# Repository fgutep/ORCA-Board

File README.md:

<div align="center">

<br>

**Tarjeta de control abierta para robots con ROS 2, pensada para ser la base electrónica compartida de los robots de la universidad.**

<br>

[Resumen](#resumen) · [Características](#características) · [Estado](#estado-del-proyecto) · [Integración en robots](#integración-en-robots) · [Inicio rápido](#inicio-rápido) · [Estructura](#estructura-del-repositorio) · [Simulación](#simulación-de-la-etapa-de-potencia) · [Equipo](#equipo) · [Licencia](#licencia)

</div>

---

## Resumen

En la robótica académica cada proyecto suele diseñar desde cero su electrónica de potencia, actuación y sensado, y después improvisa puentes para conectarla con ROS 2. Eso repite el mismo trabajo de hardware y firmware en cada equipo. Las tarjetas comerciales de referencia, como la Acebott V3 o la Hiwonder RCB, aceptan como máximo baterías 2S o 3S, no siempre traen bus CAN y necesitan un computador intermedio para hablar con ROS.

**ORCA-Board** (*Open Robotics Control Architecture*) es una tarjeta de control abierta pensada para funcionar como nodo nativo de ROS 2 con micro-ROS. Se alimenta con baterías LiPo de **2S a 6S (7.4 a 25.2 V)** y reúne en una sola placa lo que un robot móvil o un brazo necesitan para actuar, sentir y comunicarse. El objetivo del proyecto es diseñar, fabricar y verificar esta plataforma para que distintos robots compartan la misma base electrónica.

<table>
  <tr>
    <td align="center" width="33%"><br><sub><b>Placa de control</b> · ESP32-S3</sub></td>
    <td align="center" width="33%"><br><sub><b>Placa de potencia</b> · LM5175</sub></td>
    <td align="center" width="33%"><br><sub><b>Layout PCB</b> · placa de control (KiCad)</sub></td>
  </tr>
</table>

## Características

El sistema se divide en **dos PCB de 4 capas** diseñadas en KiCad.

### Placa de control

| Función | Componente |
|---|---|
| Microcontrolador | ESP32-S3-WROOM-1-N4 (Wi-Fi, BLE y USB nativo; 4 MB de flash, sin PSRAM) |
| Motores DC | 2 × drivers DRV8874 |
| Servos | 16 canales PWM con PCA9685 |
| IMU | BNO085 de 9 ejes |
| Voltaje de batería | INA226 |
| Corriente de batería | ACS725 |
| Bus CAN | Transceptor SN65HVD230 |
| Sensores externos | Multiplexor I²C TCA9548A (4 canales: J14–J17) |
| Alimentación lógica | Buck TPS54331D a 5 V y regulador de 3.3 V |

### Placa de potencia

Convertidor **buck-boost LM5175** para el riel de motores: entrada de 6 a 25.2 V, salida ajustable de 6.8 a 25 V y hasta 8 A.

| Función | Componente |
|---|---|
| Controlador | U1: LM5175PWPR, controlador buck-boost de 4 interruptores |
| Interruptores de potencia | Q1–Q4: MOSFET de canal N de 40 V en LFPAK56 (Nexperia BUK9Y3R5-40E, marcado 93E540) |
| Inductor | L1: Pulse PA4344, 4.7 µH |
| Sensado de corriente | R12: shunt Kelvin de 5 mΩ (2512) |
| Condensadores de potencia | Entrada: C2, 100 µF · Salida: C19 y C20, 220 µF · Cerámicos de 10 µF: C4, C14 y C15 |
| Ajuste de VOUT | Divisor de realimentación (R13 49.9 kΩ, R14 1.65 kΩ) y trimmer RV1 |
| Diodos | D1–D3: Schottky B5819W (bootstrap) |
| Conectores | J1 y J2: XT60 (entrada de batería y salida al riel de motores) |

### Mapa de pines (control Rev A)

| Bus / señal | Pines |
|---|---|
| I²C de placa (INA226 `0x40`, PCA9685 `0x41`, BNO085 `0x4A`/`0x4B`) | SDA `IO18` · SCL `IO17` |
| I²C externo (TCA9548A `0x70`) | SDA `IO39` · SCL `IO38` · RESET `IO40` |
| Sensor de corriente ACS725 | `IO9` |
| CAN (500 kbit/s) | TX `IO6` · RX `IO7` |

## Estado del proyecto

| Parte | Estado |
|---|---|
| **Placa de control, Rev A** | ✅ Fabricada y operativa. Autoprueba: **8 pruebas aprobadas, 0 fallas** |
| BNO085 | ✅ Montado (U1) y usado por el firmware micro-ROS (`/imu`) |
| Placa de potencia (LM5175), Placa 2 | ✅ Caracterizada con carga hasta 198.7 W en boost ([registro](Hardware-Potencia/pruebas_carga/registro.md)). Corta solo en la zona de transición (Vin ≈ Vout). Alimentó los motores a 12 V con la entrada barrida de 8 a 24 V |
| Placa de potencia (LM5175), Placa 1 | 🔴 LM5175 defectuoso de fábrica ([registro](Hardware-Potencia/physical_debug/README.md)) |
| Drivers de motor (DRV8874) | ✅ Probados con N20 y Faulhaber a 12 V en el banco de motores ([ensayo](Hardware/physical_debug/11_ensayo_motores_N20_Faulhaber.md)) |
| micro-ROS sobre la placa | ✅ Firmware de uso general ([`firmware/orca_micro_ros`](firmware/orca_micro_ros/README.md)): nodo `/orca_board` en ROS 2 Jazzy con batería, IMU, diagnóstico, motores, servos, puente CAN a 25 kbit/s (`can_msgs/Frame`) y parámetros persistentes, con transportes USB y Wi-Fi. Probado por USB y por Wi-Fi en la integración con SWARM; falta probar CAN contra otro nodo |
| Integración en robots | ✅ Robot del enjambre SWARM y robot diferencial con ROS 2 ([ver sección](#integración-en-robots)) |

### Resultados de la placa de control

| Prueba | Resultado medido | Estado |
|---|---|:---:|
| USB-C nativo | Enumera como `303a:1001`; flasheo con hash verificado | ✅ |
| Alimentación | Riel de 3.3 V estable; VBUS de 8 a 22 V con Wi-Fi activo | ✅ |
| Bus I²C | Detecta `0x40` (INA226), `0x41` (PCA9685) y `0x70` (TCA9548A) | ✅ |
| INA226 · V batería | ID `0x5449` leído; Vbus medido = 8.001 V | ✅ |
| PCA9685 · 16 PWM | Escritura y lectura de registros correcta | ✅ |
| ACS725 · corriente | Cero calibrado en 319 mV, sensibilidad 264 mV/A | ✅ |
| CAN · SN65HVD230 | Eco a 500 kbit/s con 0 errores de bus | ✅ |
| Telemetría Wi-Fi | Autoprueba servida en `http://192.168.4.1` | ✅ |

<table>
  <tr>
    <td align="center" width="50%"><br><sub><b>Termografía con VBUS</b> · máx. 39.6 °C</sub></td>
    <td align="center" width="25%"><h1>8/8</h1><sub>pruebas aprobadas en la autoprueba (0 fallas)</sub></td>
    <td align="center" width="25%"><h1>8–22 V</h1><sub>VBUS estable con telemetría Wi-Fi activa</sub></td>
  </tr>
</table>

La termografía con VBUS dio un máximo de 39.6 °C. El detalle del bring-up, con errata y retrabajos incluidos, está en [`Hardware/physical_debug`](Hardware/physical_debug/README.md).

## Integración en robots

### Enjambre SWARM

La placa de control ORCA, integrada a un robot SWARM, respondió correctamente a señales de movimiento enviadas por Wi-Fi desde ROS 2 corriendo en una Raspberry Pi 5 que tenía esclavizada a la placa de lógica. Video de la validación: [youtu.be/ohQkxq8agtg](https://youtu.be/ohQkxq8agtg).

<table>
  <tr>
    <td align="center" width="50%"><br><sub>Robot SWARM antes de integrar ORCA</sub></td>
    <td align="center" width="50%"><br><sub>Robot SWARM con ORCA integrada</sub></td>
  </tr>
</table>

### Robot diferencial

ORCA en un robot diferencial con micro-ROS, ROS 2 y reconocimiento visual tipo TurtleBot. Video: [youtube.com/shorts/Cfd5DdbkZio](https://youtube.com/shorts/Cfd5DdbkZio).

<table>
  <tr>
    <td align="center" width="50%"></td>
    <td align="center" width="50%"></td>
  </tr>
</table>

## Inicio rápido

### 1. Flashear el firmware de autoprueba

El firmware vive en [`Hardware/physical_debug/`](Hardware/physical_debug/). La imagen más completa es [`orca_selftest`](Hardware/physical_debug/orca_selftest/orca_selftest.ino).

**Arduino IDE** (Herramientas →):

| Opción | Valor |
|---|---|
| Placa | ESP32S3 Dev Module |
| USB Mode | Hardware CDC and JTAG |
| USB CDC On Boot | **Enabled** |
| Flash Mode / Size | QIO 80MHz / 4MB (32Mb) |
| Partition Scheme | Default 4MB with spiffs |

**PlatformIO**: el proyecto de [`platformio_bringup/`](Hardware/physical_debug/platformio_bringup/platformio.ini) ya trae la configuración de la placa.

```bash
cd Hardware/physical_debug/platformio_bringup
pio run -t upload
pio device monitor        # 115200 baudios por el USB nativo
```

### 2. Ver la autoprueba

Cada 5 s la placa corre todas las pruebas y publica el informe por **USB** y por **Wi-Fi**.

1. Conéctate a la red `ORCA-Board` (la clave está en el sketch; cámbiala si vas a usar la placa fuera del laboratorio).
2. Abre **http://192.168.4.1/** para ver el informe en vivo.
3. Opcional: `/status.json` (telemetría y resultados) y `/report.txt` (informe en texto).

### 3. Registrar telemetría desde el PC

```bash
python3 Hardware/physical_debug/wifi_telemetry/orca_monitor.py --csv prueba.csv
```

Solo usa la biblioteca estándar de Python, guarda todo en CSV y avisa si la placa deja de responder o se reinicia.

## Estructura del repositorio

```text
ORCA-Board/
├── Hardware/                  PCB de control (KiCad): esquemáticos, PCB, footprints y gerbers
│   └── physical_debug/        Bring-up de la placa fabricada: documentos 01–09 y firmware de prueba
├── Hardware-Potencia/         PCB de potencia LM5175 (KiCad) y su bring-up
│   ├── jlcpcb/                Archivos de fabricación y BOM de potencia (production_files/)
│   ├── pruebas_carga/         Script, registro y datos de las pruebas de carga
│   └── physical_debug/        Protocolo de arranque por etapas y diagnóstico
├── simulacion/                Modelos y simulaciones LTspice del buck-boost
│   ├── scripts/               Análisis y gráficas en Python
│   └── resultados/            Figuras de las corridas
├── firmware/
│   └── orca_micro_ros/        Firmware micro-ROS (ROS 2 Jazzy) de uso general
├── examples/                  Ejemplos de uso de la placa (brazo por gestos con IMU y servos)
├── Datasheets/                Hojas de datos de los componentes
├── Prints/                    Esquemático y layout de la placa de potencia en PDF/PNG
└── docs/img/                  Imágenes de este README
```

## Simulación de la etapa de potencia

<p align="center">
  <br>
  <sub><b>Layout PCB</b> · placa de potencia, cara superior (KiCad)</sub>
</p>

La carpeta [`simulacion/`](simulacion/) contiene el modelo LTspice del LM5175 y el barrido de **4 esquinas** (corrida del 29-ago) con escalón de carga de 2 A a 8.4 A a los 24 ms, contrastado con los límites de diseño de 8 A continuos y 15 A de pico en el inductor.

| VIN | VOUT esperado | VOUT simulado | Desviación | I_L pico | Pin | Pout | Eficiencia |
|---|---|---|---|---|---|---|---|
| 6 V | 7.2 V | 7.199 V | −0.01 % | 13.0 A | 69.4 W | 60.5 W | 87.2 % |
| 12 V | 12 V | 11.999 V | −0.01 % | 11.2 A | 109.0 W | 100.8 W | 92.4 % |
| 22.2 V | 25 V | 24.997 V | −0.01 % | 14.3 A | 219.4 W | 210.0 W | 95.7 % |
| 25.2 V | 7.2 V | 7.199 V | −0.01 % | 10.8 A | 69.2 W | 60.5 W | 87.4 % |

Las cuatro esquinas regulan dentro de ±0.01 % y mantienen el pico del inductor bajo 15 A (el menor margen es 0.7 A, en 22.2 → 25 V). VOUT simulado, Pin, Pout y eficiencia se miden en la ventana de 27 a 28 ms, con el escalón de carga aplicado. Datos completos en [`simulacion/resultados/c2_4esquinas_resumen.csv`](simulacion/resultados/c2_4esquinas_resumen.csv).

> **Nota sobre el barrido de 16 esquinas (28-ago).** Fue una corrida preliminar y se descartó como referencia: los cuatro casos de VIN = 6 V no arrancan (VOUT final de −1.55 V) y en los demás el pico del inductor llega a 34–37 A, por encima del límite de 15 A. Ese export tampoco registra la corriente de entrada, así que no permite calcular Pin ni eficiencia. Sus resultados siguen en [`simulacion/resultados/c1_16esquinas_resumen.csv`](simulacion/resultados/c1_16esquinas_resumen.csv) y su gráfica en [`c1_16esquinas_resumen.png`](simulacion/resultados/c1_16esquinas_resumen.png) solo como registro. La referencia vigente es la de 4 esquinas.

### Simulación frente a pruebas físicas

Las pruebas de carga se hicieron sobre la Placa 2 el 23 y 24 de noviembre, con la carga electrónica Rigol DL3021, la fuente EA PS 10060-170 y la cámara térmica Keysight U5855A. El detalle de cada corrida está en el [registro](Hardware-Potencia/pruebas_carga/registro.md).

**Pruebas realizadas**

| Corrida | VIN → VOUT | Tipo de prueba | Carga aplicada | Eficiencia medida |
|---|---|---|---|---|
| R08 | 12 → 12 V | Escalones de 0.5 A cada 30 s | 0.5 a 4.5 A (6 a 54 W) | 71.5 a 92.3 % |
| R09 | 16 → 12 V | Escalones de 0.25 A cada 20 s | 3 a 5 A (36 a 59.5 W) | 89.6 a 90.7 % |
| R10 | 9 → 12 V | Escalones de 0.25 A cada 20 s | 3 a 5 A (36 a 59.5 W) | 87.0 a 90.4 % |
| R11 | 20 → 12 V | Escalones de 0.25 A cada 20 s | 3 a 5 A (36 a 59.5 W) | 88 a 92 % |
| R12 a R15 | 10.5, 11, 13 y 14 → 12 V | Mapeo de la zona de transición | 4 a 5 A (48 a 60 W) | 89.5 a 92.0 % |
| R16 | 9 → 12 V | Carga sostenida durante 10 min | 5 A (59.5 W) | 87.0 %, máximo de 71 °C |
| R17 | 25.2 → 7.2 V | Escalones de 1 A cada 20 s | 1 a 5 A (7.2 a 35.3 W) | 56.9 a 82.4 % |
| R18 | 6 → 7.2 V | Escalones de 1 A cada 20 s | 1 a 5 A (7.2 a 35.3 W) | 82.9 a 88.2 % |
| R19, R20 | 22.2 → 25 V | Escalones de 1 A y de 0.25 A | 1 a 2.75 A (25 a 68.7 W) | 86.7 a 91.1 % |
| R21 | 18 → 25 V | Escalones hasta 7 A cada 10 s | 1 a 7 A (25 a 174.4 W) | 86.9 a 92.5 % |
| R22 | 18 → 25 V | Escalones hasta 7.98 A cada 10 s | 2 a 7.98 A (50 a 198.7 W) | 87.6 a 91.0 % |

**Comparación por esquina de diseño**

La simulación evalúa cada esquina con 8.4 A de salida. En el banco la carga se subió por escalones, así que cada fila compara la simulación con el punto de mayor potencia medido en esa esquina.

| Esquina | Modo | Pout simulada | Pout medida | η simulada | η medida | η máxima medida | VOUT simulado | VOUT medido | Corrida |
|---|---|---|---|---|---|---|---|---|---|
| 6 → 7.2 V | Boost | 60.5 W | 35.3 W | 87.2 % | 82.9 % | 88.2 % (14.3 W) | 7.199 V | 7.063 V | R18 |
| 12 → 12 V | Transición | 100.8 W | 54 W | 92.4 % | 90.5 a 91.6 % | 92.3 % (30 W) | 11.999 V | 11.908 V | R08 |
| 22.2 → 25 V | Boost | 210.0 W | 68.7 W | 95.7 % | 91.1 % | 91.1 % (68.7 W) | 24.997 V | 24.998 V | R20 |
| 25.2 → 7.2 V | Buck | 60.5 W | 35.3 W | 87.4 % | 82.4 % | 82.4 % (35.3 W) | 7.199 V | 7.062 V | R17 |

Fuera de las cuatro esquinas, con 18 → 25 V, la placa entregó 124.8 W con η = 91.2 % y llegó a **198.7 W** con η = 87.6 % y VOUT = 24.897 V (R21 y R22).

**Diferencias entre el modelo y el banco**

| Aspecto | Simulación (LTspice) | Banco (Placa 2) | Origen de la diferencia |
|---|---|---|---|
| Regulación de VOUT | ±0.01 % | Cae entre 0.1 % y 2 % a plena carga | La medición incluye los conectores y el cableado de salida, que el modelo no tiene |
| Eficiencia | 87.2 a 95.7 % | 82.4 a 92.3 % | Pérdidas en los cables de entrada (hasta 7.6 A de Iin) y resolución de 0.1 A de la fuente en Iin (±1 a 3 % de η). En las esquinas de 7.2 V pesa más la pérdida fija de conmutación |
| Potencia | 60.5 a 210 W, con 8.4 A de salida | Hasta 198.7 W en 18 → 25 V | En el banco la carga se subió por escalones hasta el punto de mayor potencia de cada prueba |
| Temperatura | No se modela | 71 °C tras 10 min a 59.5 W; punto caliente en los MOSFET Q3/Q4 del lado de VOUT | El modelo LTspice no incluye comportamiento térmico ([fotos térmicas](Hardware-Potencia/pruebas_carga/fotos_termicas/)) |

## Documentación

| Qué | Dónde |
|---|---|
| Bring-up de la placa de control | [`Hardware/physical_debug/README.md`](Hardware/physical_debug/README.md) |
| Firmware micro-ROS (tópicos, parámetros, seguridad) | [`firmware/orca_micro_ros/README.md`](firmware/orca_micro_ros/README.md) |
| Bring-up de la placa de potencia | [`Hardware-Potencia/physical_debug/README.md`](Hardware-Potencia/physical_debug/README.md) |
| BOM de la placa de control (JLCPCB, carrito del 23-sep-2026) | [`Hardware/BOM-ORCA-BOARD-control.csv`](Hardware/BOM-ORCA-BOARD-control.csv) |
| BOM de la placa de potencia | [`Hardware-Potencia/jlcpcb/production_files/BOM-ORCA-BOARD.csv`](Hardware-Potencia/jlcpcb/production_files/BOM-ORCA-BOARD.csv) |
| Pruebas de carga de la placa de potencia | [`Hardware-Potencia/pruebas_carga/registro.md`](Hardware-Potencia/pruebas_carga/registro.md) |
| Manual de usuario (guía de inicio rápido y de seguridad) | [`docs/manual/ORCA-Board_Manual_de_usuario.pdf`](docs/manual/ORCA-Board_Manual_de_usuario.pdf) |
| Ejemplos de uso | [`examples/README.md`](examples/README.md) |
| Hojas de datos | [`Datasheets/`](Datasheets/) |
| Esquemático y layout de potencia | [`Prints/`](Prints/) |

## Equipo

Proyecto de la Facultad de Ingeniería de la Universidad de los Andes, presentado en la Semana de la Innovación.

| Autor |
|---|
| Juan Angulo |
| Felipe Gutiérrez |
| Luis Aristizábal |

<details>
<summary><b>Ver el póster de la Semana de la Innovación</b></summary>
<br>

</details>

## Licencia

Este proyecto se distribuye bajo la [licencia MIT](LICENSE).

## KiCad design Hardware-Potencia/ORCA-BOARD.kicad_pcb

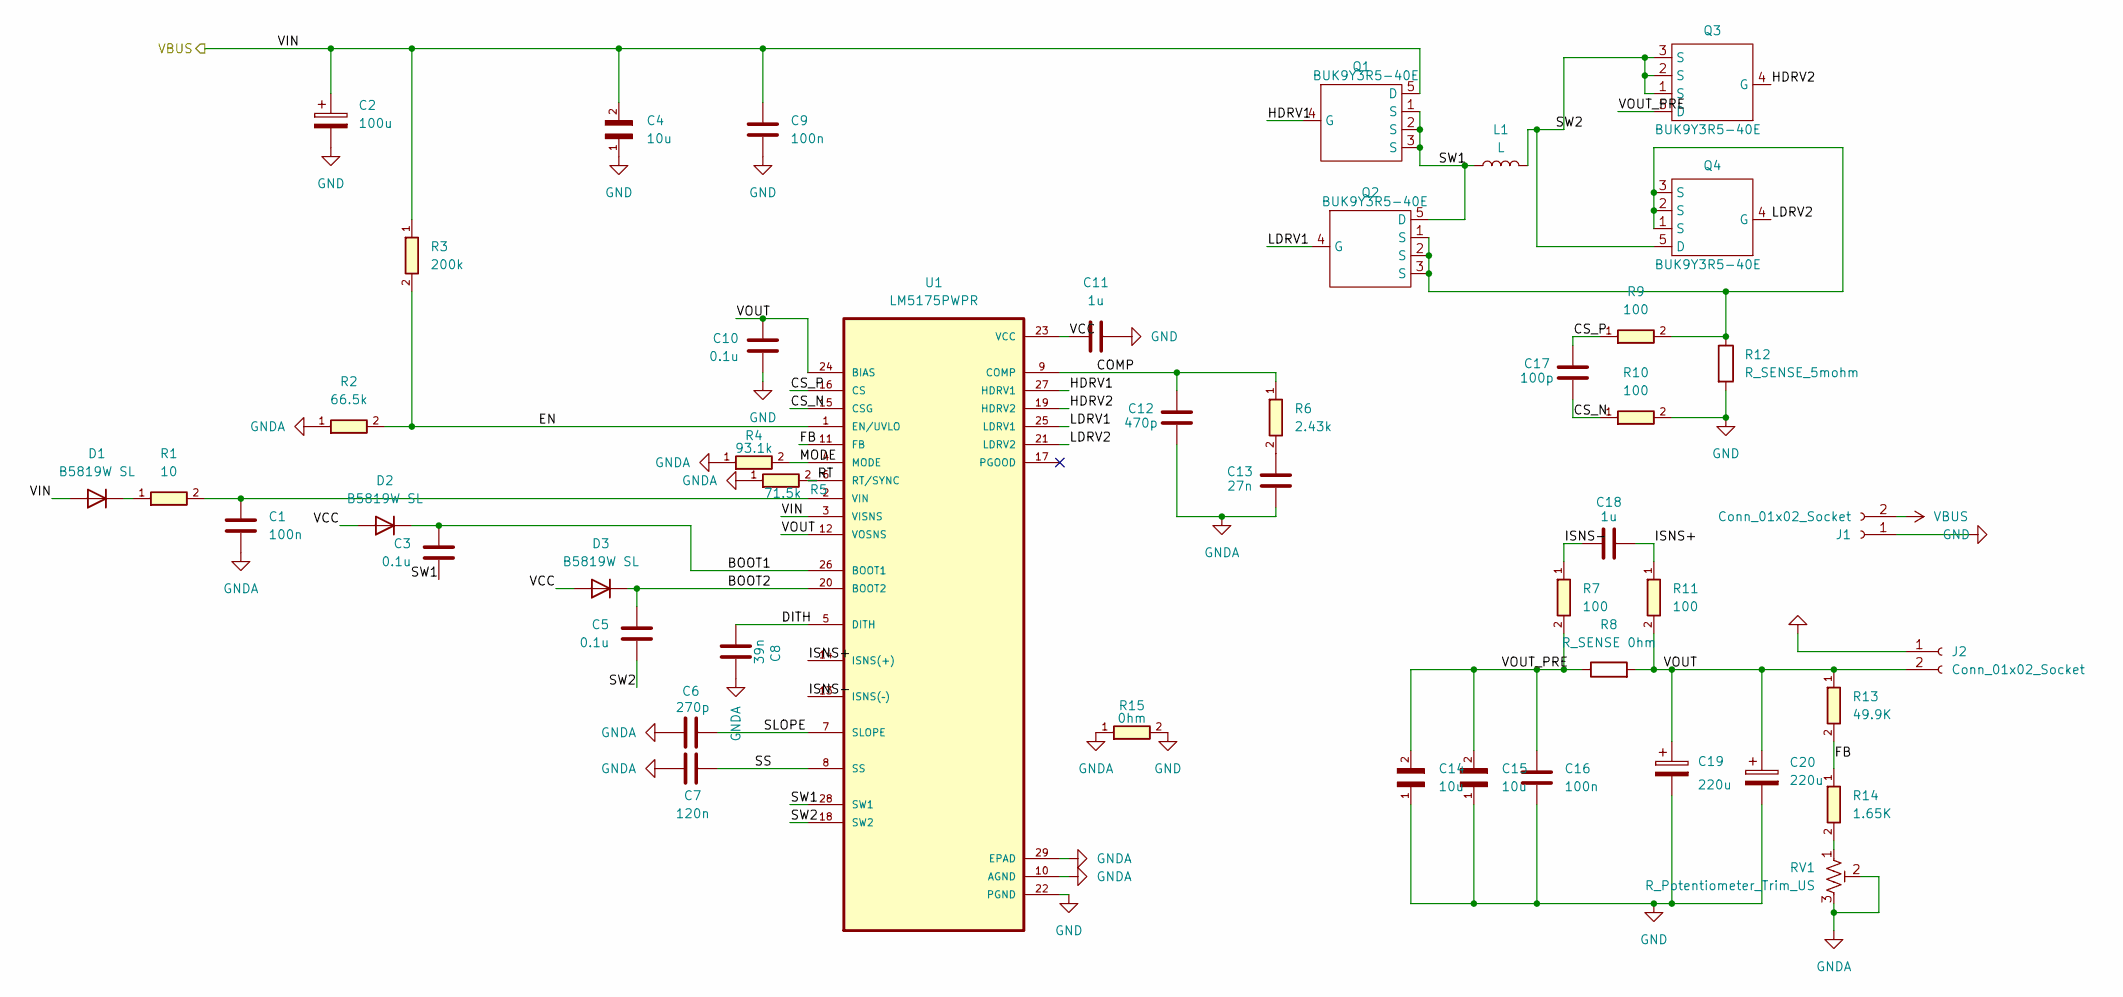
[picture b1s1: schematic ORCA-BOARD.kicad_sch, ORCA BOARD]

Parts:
C1: 100n; 0603; LCSC C1591
C2: 100u; CP_Radial_D8.0mm_P3.50mm; LCSC C171434
C3, C5, C10: 0.1u; 0603; LCSC C1591
C4, C14, C15: 10u; CAPC3225X280N; LCSC C18739
C6: 270p; 0603; LCSC C1657
C7: 120n; 0603; LCSC C282672
C8: 39n; 0603; LCSC C107091
C9, C16: 100n; CAPC3225X280N; LCSC C76567
C11, C18: 1u; CAPC2012X100N; LCSC C28323
C12: 470p; 0603; LCSC C36252
C13: 27n; 0603; LCSC C107086
C17: 100p; 0603; LCSC C14858
C19, C20: 220u; CP_Radial_D8.0mm_P3.50mm; LCSC C48970419
D1, D2, D3: B5819W SL; D_SOD-123; LCSC C8598
J1, J2: Conn_01x02_Socket; AMASS_XT60-F_1x02_P7.20mm_Vertical; LCSC C98734
L1: L; L_Pulse_PA4344; LCSC C2453762
Q1, Q2, Q3, Q4: BUK9Y3R5-40E; LFPAK56; MPN BUK9Y3R5-40E; LCSC C553274
R1: 10; 0603; LCSC C22859
R2: 66.5k; 0603; LCSC C23225
R3: 200k; 0603; LCSC C25811
R4: 93.1k; 0603; LCSC C305035
R5: 71.5k; 0603; LCSC C23103
R6: 2.43k; 0603; LCSC C22906
R7, R9, R10, R11: 100; 0603; LCSC C22775
R8: R_SENSE 0hm; RES_1-2176421-2; LCSC C556651
R12: R_SENSE_5mohm; R_2512_Kelvin_TLRP; LCSC C393074
R13: 49.9K; 0603; LCSC C705780
R14: 1.65K; 0603; LCSC C705743
R15: 0hm; 0603; LCSC C15402
RV1: R_Potentiometer_Trim_US; Potentiometer_Bourns_3296W_Vertical; LCSC C60620
U1: LM5175PWPR; LM5175PWP; LCSC C113356

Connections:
/BOOT1: C3.1, D2.1 (K), U1.26 (BOOT1)
/BOOT2: C5.1, D3.1 (K), U1.20 (BOOT2)
/COMP: C12.2, R6.1, U1.9 (COMP)
/CS_N: C17.1, R10.1, U1.15 (CSG)
/CS_P: C17.2, R9.1, U1.16 (CS)
/DITH: C8.2, U1.5 (DITH)
/EN: R2.2, R3.2, U1.1 (EN/UVLO)
/FB: R13.2, R14.1, U1.11 (FB)
/HDRV1: Q1.4 (G), U1.27 (HDRV1)
/HDRV2: Q3.4 (G), U1.19 (HDRV2)
/ISNS+: C18.2, R11.1, U1.14 (ISNS(+))
/ISNS-: C18.1, R7.1, U1.13 (ISNS(–))
/LDRV1: Q2.4 (G), U1.25 (LDRV1)
/LDRV2: Q4.4 (G), U1.21 (LDRV2)
/MODE: R4.2, U1.4 (MODE)
/RT: R5.2, U1.6 (RT/SYNC)
/SLOPE: C6.2, U1.7 (SLOPE)
/SS: C7.2, U1.8 (SS)
/SW1: C3.2, L1.1, Q1.1 (S), Q1.2 (S), Q1.3 (S), Q2.5 (D), U1.28 (SW1)
/SW2: C5.2, L1.2, Q3.1 (S), Q3.2 (S), Q3.3 (S), Q4.5 (D), U1.18 (SW2)
/VCC: C11.1, D2.2 (A), D3.2 (A), U1.23 (VCC)
/VOUT: C10.1, C19.1, C20.1, J2.2, R8.2, R11.2, R13.1, U1.12 (VOSNS), U1.24 (BIAS)
/VOUT_PRE: C14.2, C15.2, C16.1, Q3.5 (D), R7.2, R8.1
GND: C2.2, C4.1, C9.2, C10.2, C11.2, C14.1, C15.1, C16.2, C19.2, C20.2, J1.1, J2.1, R10.2, R12.2, R15.2, U1.22 (PGND)
GNDA: C1.2, C6.1, C7.1, C8.1, C12.1, C13.1, R2.1, R4.1, R5.1, R15.1, RV1.2, RV1.3, U1.10 (AGND), U1.29 (EPAD)
unnamed: C13.2, R6.2
unnamed: D1.1 (K), R1.1
unnamed: Q2.1 (S), Q2.2 (S), Q2.3 (S), Q4.1 (S), Q4.2 (S), Q4.3 (S), R9.2, R12.1
unnamed: R14.2, RV1.1
unnamed: C1.1, R1.2, U1.2 (VIN)
VBUS: C2.1, C4.2, C9.1, D1.2 (A), J1.2, Q1.5 (D), R3.1, U1.3 (VISNS)

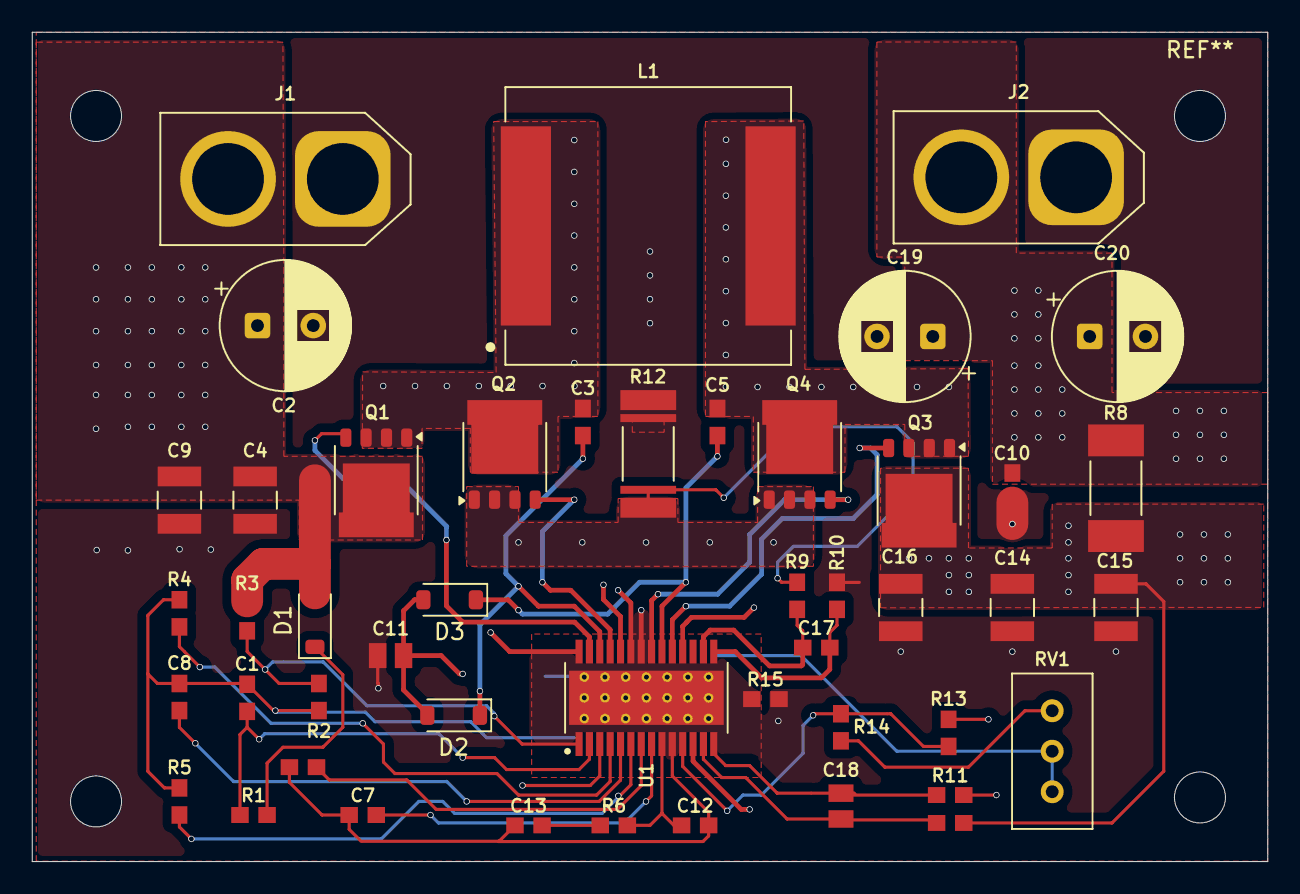
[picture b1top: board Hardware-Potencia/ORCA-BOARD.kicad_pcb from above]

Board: 4 copper layers, 77.5 x 52.0 mm, 47 parts (0 on the bottom side), 31 nets.

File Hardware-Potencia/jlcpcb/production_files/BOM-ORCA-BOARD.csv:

Comment,Designator,Footprint,LCSC,Quantity
0.1u,"C10,C3,C5",0603,C1591,3
0hm,R15,0603,C15402,1
1.65K,R14,0603,C705743,1
10,R1,0603,C22859,1
100,"R10,R11,R7,R9",0603,C22775,4
100n,C1,0603,C1591,1
100n,"C16,C9",CAPC3225X280N,C76567,2
100p,C17,0603,C14858,1
100u,C2,CP_Radial_D8.0mm_P3.50mm,C171434,1
10u,"C14,C15,C4",CAPC3225X280N,C18739,3
120n,C7,0603,C282672,1
1u,"C11,C18",CAPC2012X100N,C28323,2
2.43k,R6,0603,C22906,1
200k,R3,0603,C25811,1
220u,"C19,C20",CP_Radial_D8.0mm_P3.50mm,C48970419,2
270p,C6,0603,C1657,1
27n,C13,0603,C107086,1
39n,C8,0603,C107091,1
470p,C12,0603,C36252,1
49.9K,R13,0603,C705780,1
66.5k,R2,0603,C23225,1
71.5k,R5,0603,C23103,1
93.1k,R4,0603,C305035,1
B5819W SL,"D1,D2,D3",D_SOD-123,C8598,3
Conn_01x02_Socket,"J1,J2",AMASS_XT60-F_1x02_P7.20mm_Vertical,C98734,2
L,L1,L_Pulse_PA4344,C2453762,1
LM5175PWPR,U1,LM5175PWP,C113356,1
R_Potentiometer_Trim_US,RV1,Potentiometer_Bourns_3296W_Vertical,C60620,1
R_SENSE 0hm,R8,RES_1-2176421-2,C556651,1
R_SENSE_5mohm,R12,R_2512_Kelvin_TLRP,C393074,1
~,"Q1,Q2,Q3,Q4",LFPAK56,C553274,4

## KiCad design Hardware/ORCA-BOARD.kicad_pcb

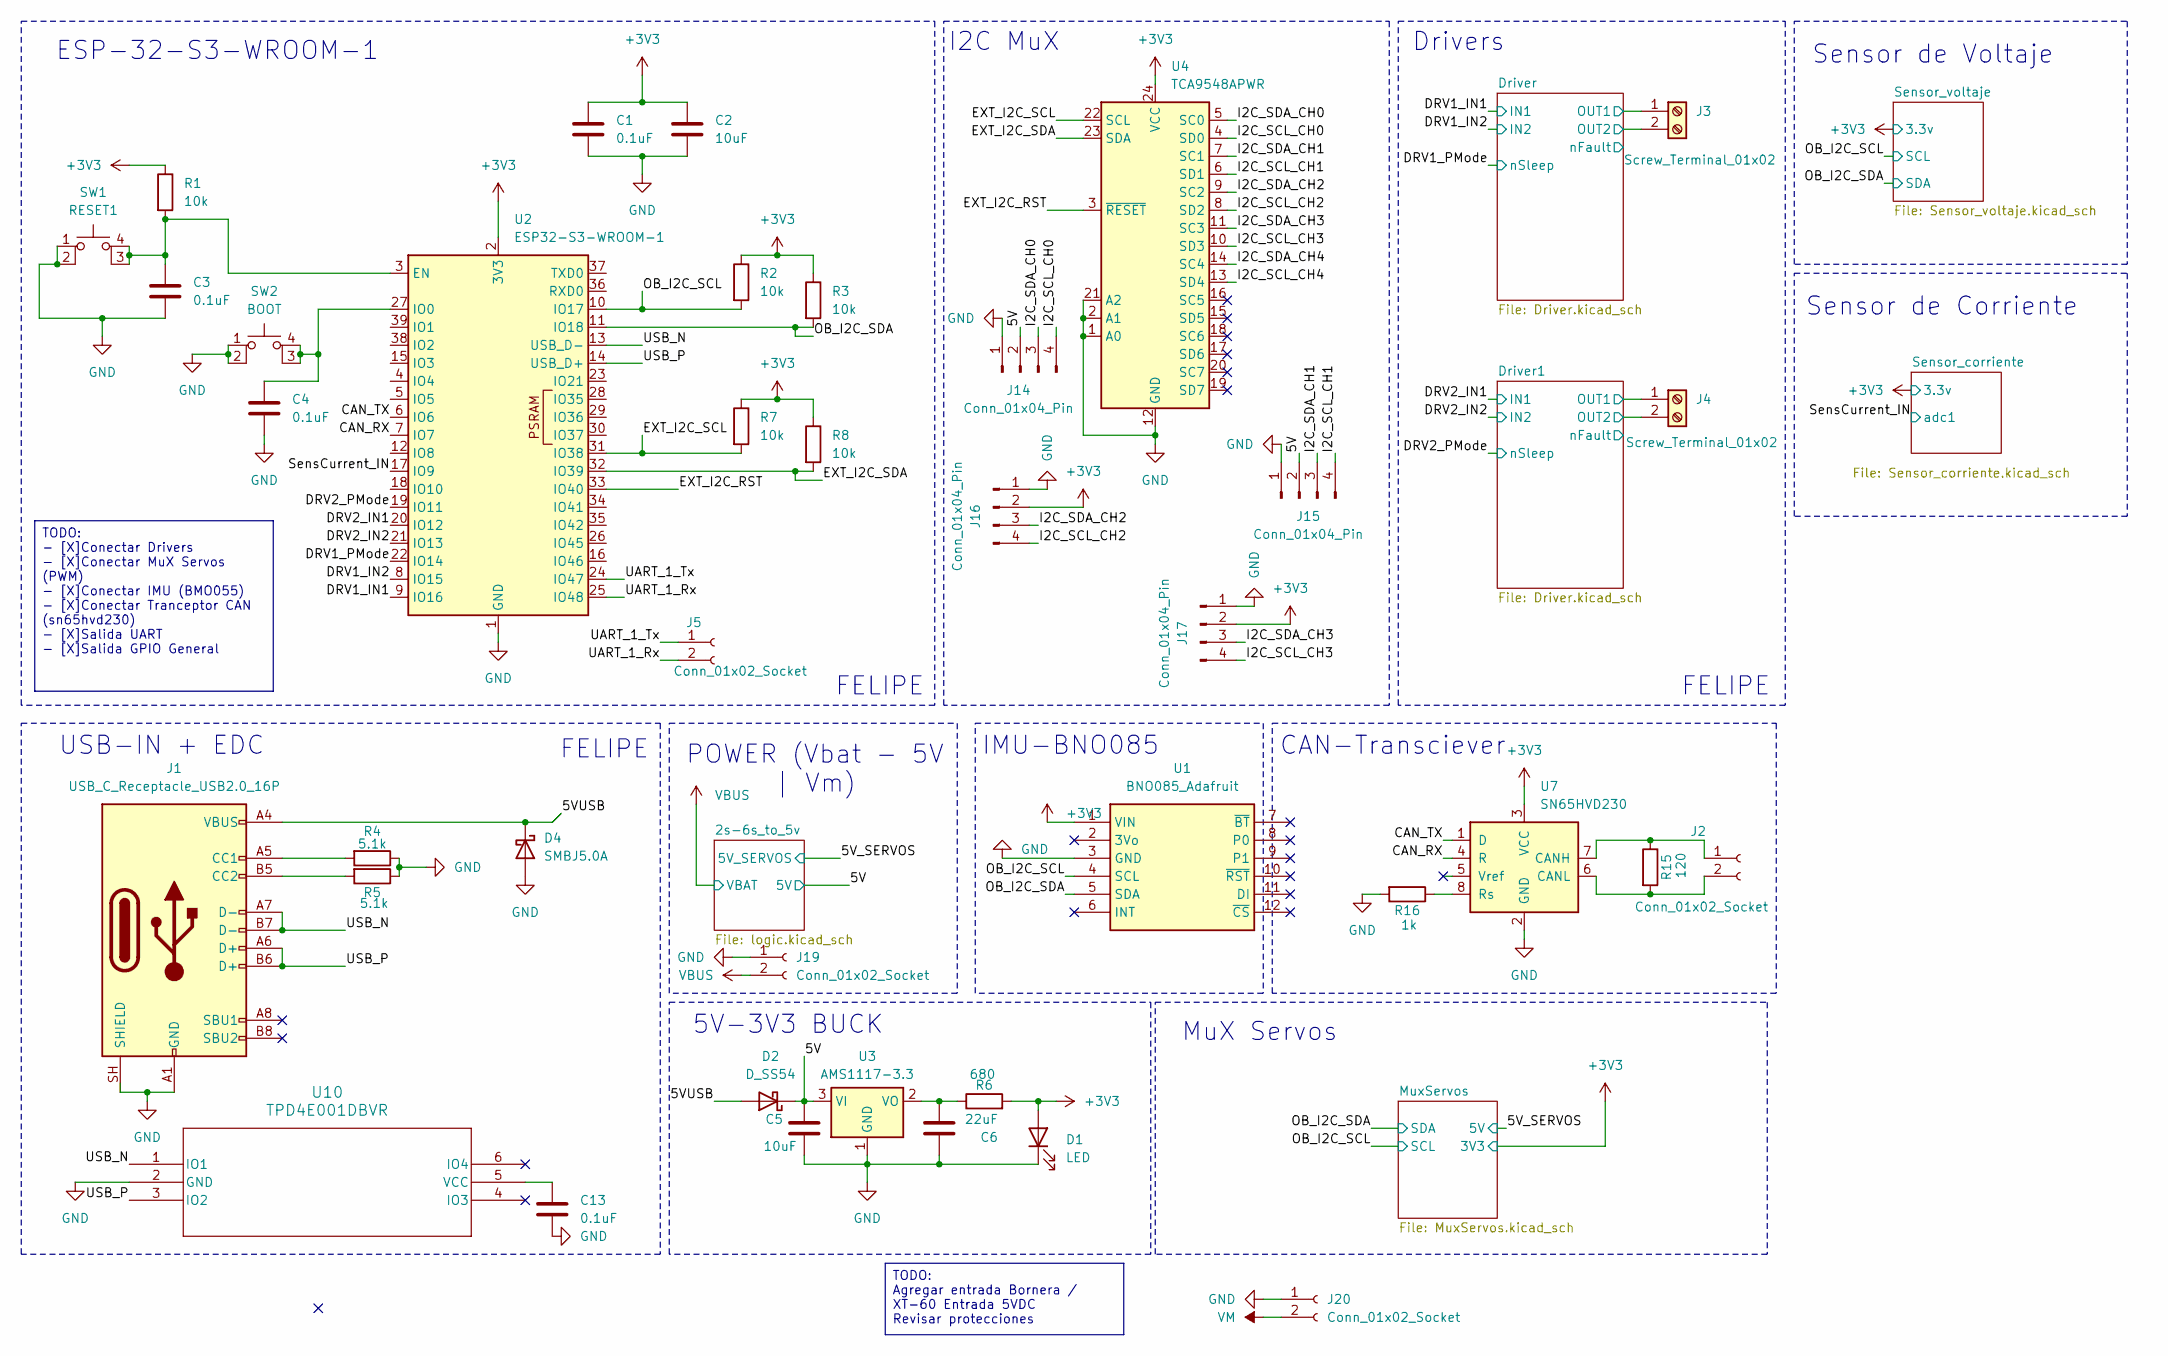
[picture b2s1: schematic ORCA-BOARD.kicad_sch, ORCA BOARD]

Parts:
C1, C3, C4, C13: 0.1uF; C_0603_1608Metric_Pad1.08x0.95mm_HandSolder
C2, C5: 10uF; C_1206_3216Metric_Pad1.33x1.80mm_HandSolder
C6: 22uF; C_1206_3216Metric_Pad1.33x1.80mm_HandSolder
D1: LED; LED_0603_1608Metric_Pad1.05x0.95mm_HandSolder
D2: D_SS54; D_SMA_Handsoldering
D4: SMBJ5.0A; D_SMB
J1: USB_C_Receptacle_USB2.0_16P; USB_C_Receptacle_GCT_USB4105-xx-A_16P_TopMnt_Horizontal
J2: Conn_01x02_Socket; JST_ZH_B2B-ZR_1x02_P1.50mm_Vertical
J3, J4: Screw_Terminal_01x02; TerminalBlock_Phoenix_MPT-0,5-2-2.54_1x02_P2.54mm_Horizontal
J5: Conn_01x02_Socket; JST_EH_B2B-EH-A_1x02_P2.50mm_Vertical
J14, J15, J16, J17: Conn_01x04_Pin; JST_EH_B4B-EH-A_1x04_P2.50mm_Vertical
J19, J20: Conn_01x02_Socket; AMASS_XT60-F_1x02_P7.20mm_Vertical
R1, R2, R3, R7, R8: 10k; LED_0603_1608Metric_Pad1.05x0.95mm_HandSolder
R4, R5: 5.1k; LED_0603_1608Metric_Pad1.05x0.95mm_HandSolder
R6: 680; LED_0603_1608Metric_Pad1.05x0.95mm_HandSolder
R15: 120; LED_0603_1608Metric_Pad1.05x0.95mm_HandSolder
R16: 1k; LED_0603_1608Metric_Pad1.05x0.95mm_HandSolder
SW1: RESET1; SW_SPST_B3S-1000_1_4_labels
SW2: BOOT; SW_SPST_B3S-1000_1_4_labels
U1: BNO085_Adafruit
U2: ESP32-S3-WROOM-1
U3: AMS1117-3.3; SOT-223-3_TabPin2
U4: TCA9548APWR; TSSOP-24_4.4x7.8mm_P0.65mm
U7: SN65HVD230; SOIC-8_3.9x4.9mm_P1.27mm
U10: TPD4E001DBVR; DBV6-M

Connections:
+3V3: C1.1, C2.1, D1.2 (A), J16.2, J17.2, R1.1, R2.1, R3.1, R6.2, R7.1, R8.1, U1.1 (VIN), U2.2 (3V3), U4.24 (VCC), U7.3 (VCC); also elsewhere on the board
/5V: C5.1, D2.1 (K), J14.2, J15.2, U3.3 (VI); also elsewhere on the board
/5VUSB: D2.2 (A), D4.1 (K), J1.A4 (VBUS), J1.A9 (VBUS), J1.B4 (VBUS), J1.B9 (VBUS)
/CAN_RX: U2.7 (IO7), U7.4 (R)
/CAN_TX: U2.6 (IO6), U7.1 (D)
/DRV1_IN1: U2.9 (IO16); also elsewhere on the board
/DRV1_IN2: U2.8 (IO15); also elsewhere on the board
/DRV1_PMode: U2.22 (IO14); also elsewhere on the board
/DRV2_IN1: U2.20 (IO12); also elsewhere on the board
/DRV2_IN2: U2.21 (IO13); also elsewhere on the board
/DRV2_PMode: U2.19 (IO11); also elsewhere on the board
/Driver1/OUT1: J4.1; also elsewhere on the board
/Driver1/OUT2: J4.2; also elsewhere on the board
/Driver/OUT1: J3.1; also elsewhere on the board
/Driver/OUT2: J3.2; also elsewhere on the board
/EXT_I2C_RST: U2.33 (IO40), U4.3 (~RESET)
/EXT_I2C_SCL: R7.2, U2.31 (IO38), U4.22 (SCL)
/EXT_I2C_SDA: R8.2, U2.32 (IO39), U4.23 (SDA)
/I2C_SCL_CH0: J14.4, U4.4 (SD0)
/I2C_SCL_CH1: J15.4, U4.6 (SD1)
/I2C_SCL_CH2: J16.4, U4.8 (SD2)
/I2C_SCL_CH3: J17.4, U4.10 (SD3)
/I2C_SCL_CH4: U4.13 (SD4)
/I2C_SDA_CH0: J14.3, U4.5 (SC0)
/I2C_SDA_CH1: J15.3, U4.7 (SC1)
/I2C_SDA_CH2: J16.3, U4.9 (SC2)
/I2C_SDA_CH3: J17.3, U4.11 (SC3)
/I2C_SDA_CH4: U4.14 (SC4)
/OB_I2C_SCL: R2.2, U1.4 (SCL), U2.10 (IO17); also elsewhere on the board
/OB_I2C_SDA: R3.2, U1.5 (SDA), U2.11 (IO18); also elsewhere on the board
/SensCurrent_IN: U2.17 (IO9); also elsewhere on the board
/UART_1_Rx: J5.2, U2.25 (IO48)
/UART_1_Tx: J5.1, U2.24 (IO47)
/USB_N: J1.A7 (D-), J1.B7 (D-), U2.13 (USB_D-), U10.1 (IO1)
/USB_P: J1.A6 (D+), J1.B6 (D+), U2.14 (USB_D+), U10.3 (IO2)
GND: C1.2, C2.2, C3.2, C4.1, C5.2, C6.1, C13.2, D1.1 (K), D4.2 (A), J1.A1 (GND), J1.A12 (GND), J1.B1 (GND), J1.B12 (GND), J1.SH (SHIELD), J14.1, J15.1, J16.1, J17.1, J19.1, J20.1, R4.1, R5.1, R16.2, SW1.1, SW1.2, SW2.1, SW2.2, U1.3 (GND), U2.1 (GND), U2.40 (GND), U2.41 (GND), U3.1 (GND), U4.1 (A0), U4.2 (A1), U4.12 (GND), U4.21 (A2), U7.2 (GND), U10.2 (GND); also elsewhere on the board
unnamed: J1.A5 (CC1), R4.2
unnamed: J1.B5 (CC2), R5.2
unnamed: J2.1, R15.1, U7.7 (CANH)
unnamed: J2.2, R15.2, U7.6 (CANL)
unnamed: C3.1, R1.2, SW1.3 (K), SW1.4 (A), U2.3 (EN)
unnamed: C4.2, SW2.3 (K), SW2.4 (A), U2.27 (IO0)
unnamed: C6.2, R6.1, U3.2 (VO)
unnamed: R16.1, U7.8 (Rs)
unnamed: C13.1, U10.5 (VCC)
VBUS: J19.2; also elsewhere on the board
VM: J20.2; also elsewhere on the board

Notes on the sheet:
FELIPE
Drivers
USB-IN + EDC
ESP-32-S3-WROOM-1
5V-3V3 BUCK
MuX Servos
Sensor de Corriente
I2C MuX
Sensor de Voltaje
POWER (Vbat - 5V | Vm)
CAN-Transciever
IMU-BNO085
TODO: Agregar entrada Bornera / XT-60 Entrada 5VDC Revisar protecciones
TODO: - [X]Conectar Drivers - [X]Conectar MuX Servos (PWM) - [X]Conectar IMU (BMO055) - [X]Conectar Tranceptor CAN (sn65hvd230) - [X]Salida UART - [X]Salida GPIO General

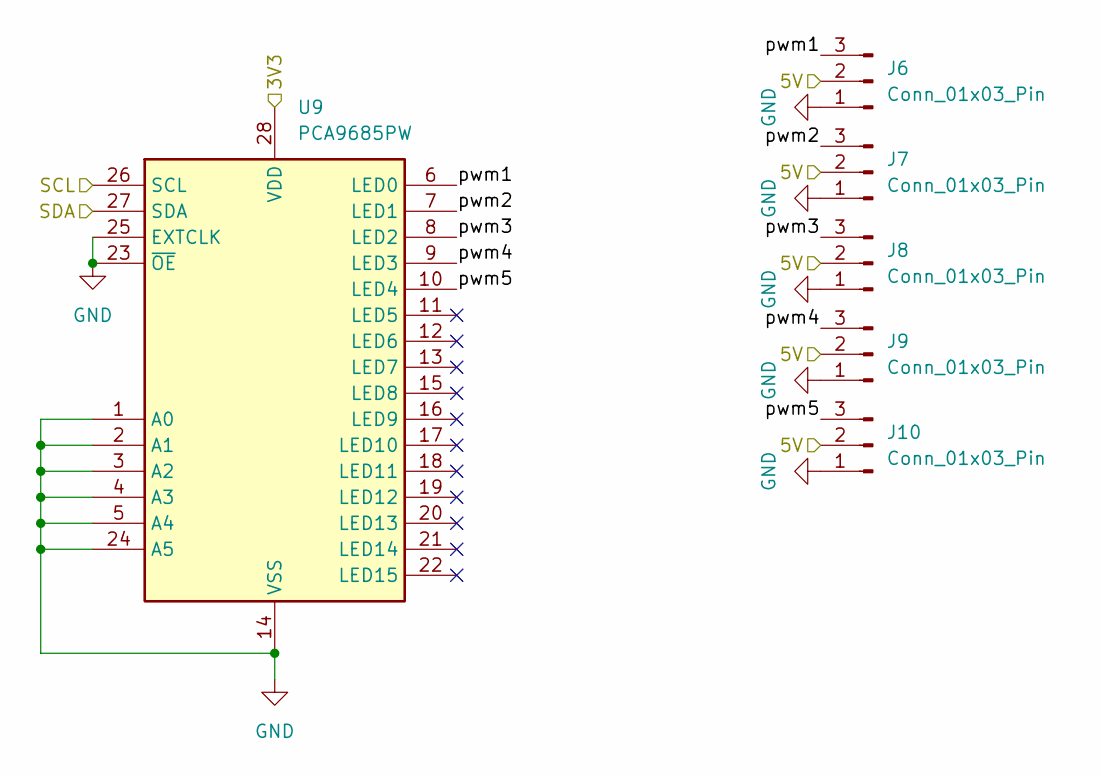
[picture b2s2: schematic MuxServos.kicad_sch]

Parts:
J6, J7, J8, J9, J10: Conn_01x03_Pin; PinHeader_1x03_P2.54mm_Vertical
U9: PCA9685PW; TSSOP-28_4.4x9.7mm_P0.65mm

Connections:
+3V3: U9.28 (VDD); also elsewhere on the board
/5V_SERVOS: J6.2, J7.2, J8.2, J9.2, J10.2; also elsewhere on the board
/MuxServos/pwm1: J6.3, U9.6 (LED0)
/MuxServos/pwm2: J7.3, U9.7 (LED1)
/MuxServos/pwm3: J8.3, U9.8 (LED2)
/MuxServos/pwm4: J9.3, U9.9 (LED3)
/MuxServos/pwm5: J10.3, U9.10 (LED4)
/OB_I2C_SCL: U9.26 (SCL); also elsewhere on the board
/OB_I2C_SDA: U9.27 (SDA); also elsewhere on the board
GND: J6.1, J7.1, J8.1, J9.1, J10.1, U9.1 (A0), U9.2 (A1), U9.3 (A2), U9.4 (A3), U9.5 (A4), U9.14 (VSS), U9.23 (~OE), U9.24 (A5), U9.25 (EXTCLK); also elsewhere on the board

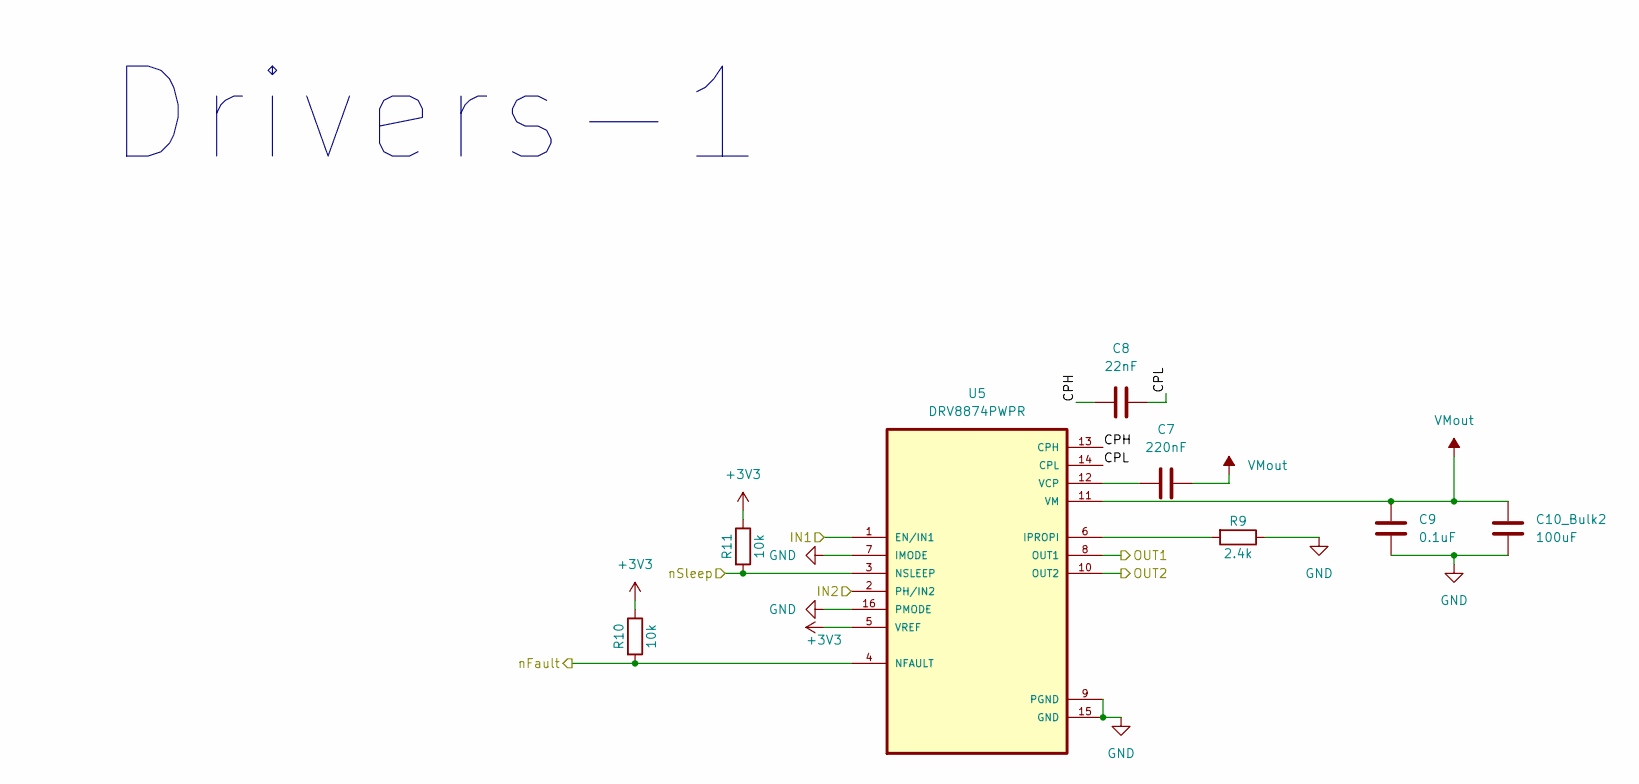
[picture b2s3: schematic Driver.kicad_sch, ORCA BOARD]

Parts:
C7: 220nF; C_0603_1608Metric_Pad1.08x0.95mm_HandSolder
C8: 22nF; C_0603_1608Metric_Pad1.08x0.95mm_HandSolder
C9: 0.1uF; C_0603_1608Metric_Pad1.08x0.95mm_HandSolder
C10_Bulk2: 100uF; CP_Elec_10x10.5
R9: 2.4k; R_0603_1608Metric_Pad0.98x0.95mm_HandSolder
R10, R11: 10k; R_0603_1608Metric_Pad0.98x0.95mm_HandSolder
U5: DRV8874PWPR; SOP65P640X120-17N

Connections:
+3V3: R10.1, R11.1, U5.5 (VREF); also elsewhere on the board
/DRV1_IN1: U5.1 (EN/IN1); also elsewhere on the board
/DRV1_IN2: U5.2 (PH/IN2); also elsewhere on the board
/DRV1_PMode: R11.2, U5.3 (NSLEEP); also elsewhere on the board
/Driver/CPH: C8.2, U5.13 (CPH)
/Driver/CPL: C8.1, U5.14 (CPL)
/Driver/OUT1: U5.8 (OUT1); also elsewhere on the board
/Driver/OUT2: U5.10 (OUT2); also elsewhere on the board
/Driver/nFault: R10.2, U5.4 (NFAULT)
GND: C9.2, C10_Bulk2.2, R9.1, U5.7 (IMODE), U5.9 (PGND), U5.15 (GND), U5.16 (PMODE); also elsewhere on the board
unnamed: R9.2, U5.6 (IPROPI)
unnamed: C7.1, U5.12 (VCP)
VMout: C7.2, C9.1, C10_Bulk2.1, U5.11 (VM); also elsewhere on the board

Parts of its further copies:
C10: 22nF; C_0603_1608Metric_Pad1.08x0.95mm_HandSolder
C10_Bulk1: 100uF; CP_Elec_10x10.5
C11: 220nF; C_0603_1608Metric_Pad1.08x0.95mm_HandSolder
C12: 0.1uF; C_0603_1608Metric_Pad1.08x0.95mm_HandSolder
R12, R13: 10k; R_0603_1608Metric_Pad0.98x0.95mm_HandSolder
R14: 2.4k; R_0603_1608Metric_Pad0.98x0.95mm_HandSolder
U6: DRV8874PWPR; SOP65P640X120-17N

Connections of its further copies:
+3V3: R12.1, R13.1, U6.5 (VREF); also elsewhere on the board
/DRV2_IN1: U6.1 (EN/IN1); also elsewhere on the board
/DRV2_IN2: U6.2 (PH/IN2); also elsewhere on the board
/DRV2_PMode: R13.2, U6.3 (NSLEEP); also elsewhere on the board
/Driver1/CPH: C10.2, U6.13 (CPH)
/Driver1/CPL: C10.1, U6.14 (CPL)
/Driver1/OUT1: U6.8 (OUT1); also elsewhere on the board
/Driver1/OUT2: U6.10 (OUT2); also elsewhere on the board
/Driver1/nFault: R12.2, U6.4 (NFAULT)
GND: C10_Bulk1.2, C12.2, R14.1, U6.7 (IMODE), U6.9 (PGND), U6.15 (GND), U6.16 (PMODE); also elsewhere on the board
unnamed: R14.2, U6.6 (IPROPI)
unnamed: C11.1, U6.12 (VCP)
VMout: C10_Bulk1.1, C11.2, C12.1, U6.11 (VM); also elsewhere on the board

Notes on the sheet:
Drivers-1

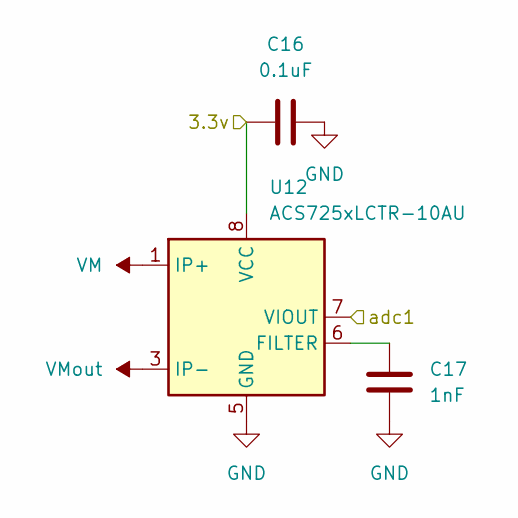
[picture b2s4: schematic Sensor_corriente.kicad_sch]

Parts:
C16: 0.1uF; C_0603_1608Metric_Pad1.08x0.95mm_HandSolder
C17: 1nF; C_0603_1608Metric_Pad1.08x0.95mm_HandSolder
U12: ACS725xLCTR-10AU; SOIC-8_3.9x4.9mm_P1.27mm

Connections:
+3V3: C16.1, U12.8 (VCC); also elsewhere on the board
/SensCurrent_IN: U12.7 (VIOUT); also elsewhere on the board
GND: C16.2, C17.2, U12.5 (GND); also elsewhere on the board
unnamed: C17.1, U12.6 (FILTER)
VM: U12.1 (IP+), U12.2 (IP+); also elsewhere on the board
VMout: U12.3 (IP-), U12.4 (IP-); also elsewhere on the board

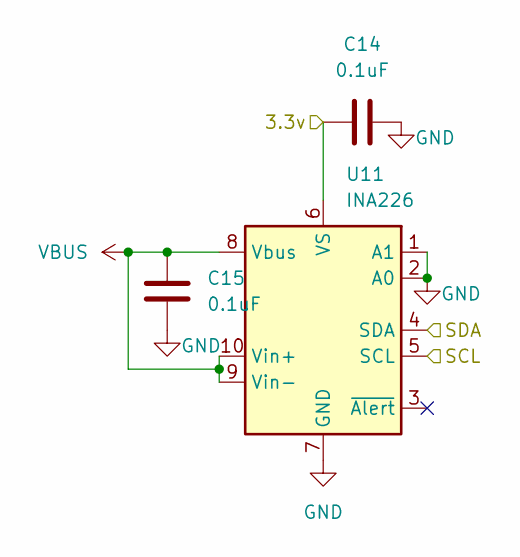
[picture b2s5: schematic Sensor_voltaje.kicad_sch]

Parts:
C14, C15: 0.1uF; C_0603_1608Metric_Pad1.08x0.95mm_HandSolder
U11: INA226; TSSOP-10_3x3mm_P0.5mm

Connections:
+3V3: C14.1, U11.6 (VS); also elsewhere on the board
/OB_I2C_SCL: U11.5 (SCL); also elsewhere on the board
/OB_I2C_SDA: U11.4 (SDA); also elsewhere on the board
GND: C14.2, C15.1, U11.1 (A1), U11.2 (A0), U11.7 (GND); also elsewhere on the board
VBUS: C15.2, U11.8 (Vbus), U11.9 (Vin-), U11.10 (Vin+); also elsewhere on the board
